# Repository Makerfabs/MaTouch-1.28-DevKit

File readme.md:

# MaTouch 1.28” ToolSets

```c++
/*
Version:		V1.0
Author:			Vincent
Create Date:	2024/9/26
Note:

*/
```

# Makerfabs

[Makerfabs home page](https://www.makerfabs.com/)

[Makerfabs Wiki](https://wiki.makerfabs.com/)

# MaTouch 1.28" DevKit

## Intruduce

MaTouch 1.28” ToolSets are series of ESP32-based products mainly consist of MaTouch 1.28” controller and kinds of functional expansion such as Dimmer/ Relay Controller/ Motor Driver, etc. It’s designed as tools to control/drive these actuators directly while also keep open hardware/software, which make it possible for users’ remaking and integration to other field projects.

[Wiki](https://wiki.makerfabs.com/Matouch%201.28%20DevKit.html)

## Part list

[Matouch 1.28" ToolSet_RGB LED Matrix](https://www.makerfabs.com/matouch-1-28-toolset-rgb-led-matrix.html)

[Matouch 1.28" ToolSet_LED Strip Controller](https://www.makerfabs.com/matouch-1-28-toolset-led-strip-controller.html)

[Matouch 1.28" ToolSet_Stepper Controller with TMC2209](https://www.makerfabs.com/matouch-1-28-toolset-stepper-controller-with-tmc2209.html)

[Matouch 1.28" ToolSet_Timer Switch Relay](https://www.makerfabs.com/matouch-1-28-toolset-timer-switch-relay.html)

[Matouch 1.28" ToolSet_DC Controller with H-Bridge](https://www.makerfabs.com/matouch-1-28-toolset-dc-controller-with-h-bridge.html)

[Matouch 1.28" ToolSet_AC Dimmer](https://www.makerfabs.com/matouch-1-28-toolset-ac-dimmer.html)

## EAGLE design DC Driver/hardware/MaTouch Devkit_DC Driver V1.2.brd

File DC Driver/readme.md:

# MaTouch1.28" Devkit DC Driver

```c++
/*
Library version:
Arduino IDE 2.3.4
esp32 V3.1.1
GFX Library for Arduino v1.5.3
lvgl v8.3.11
Adafruit INA219 v1.2.3
Adafruit BusIO v1.16.2

Tools:
USB CDC On Boot: Enabled
Flash size: 16MB(128Mb)
Partition Schrme: 16M Flash(3MB APP/9.9MB FATFS)
PSRAM: OPI PSRAM
*/
```
## Introduce

1.[How to use?](https://wiki.makerfabs.com/Matouch%201.28%20DevKit.html#26-dc-dimmer)

2.[How to upload code?](https://wiki.makerfabs.com/Matouch%201.28%20DevKit.html#36-dc-dimmer)

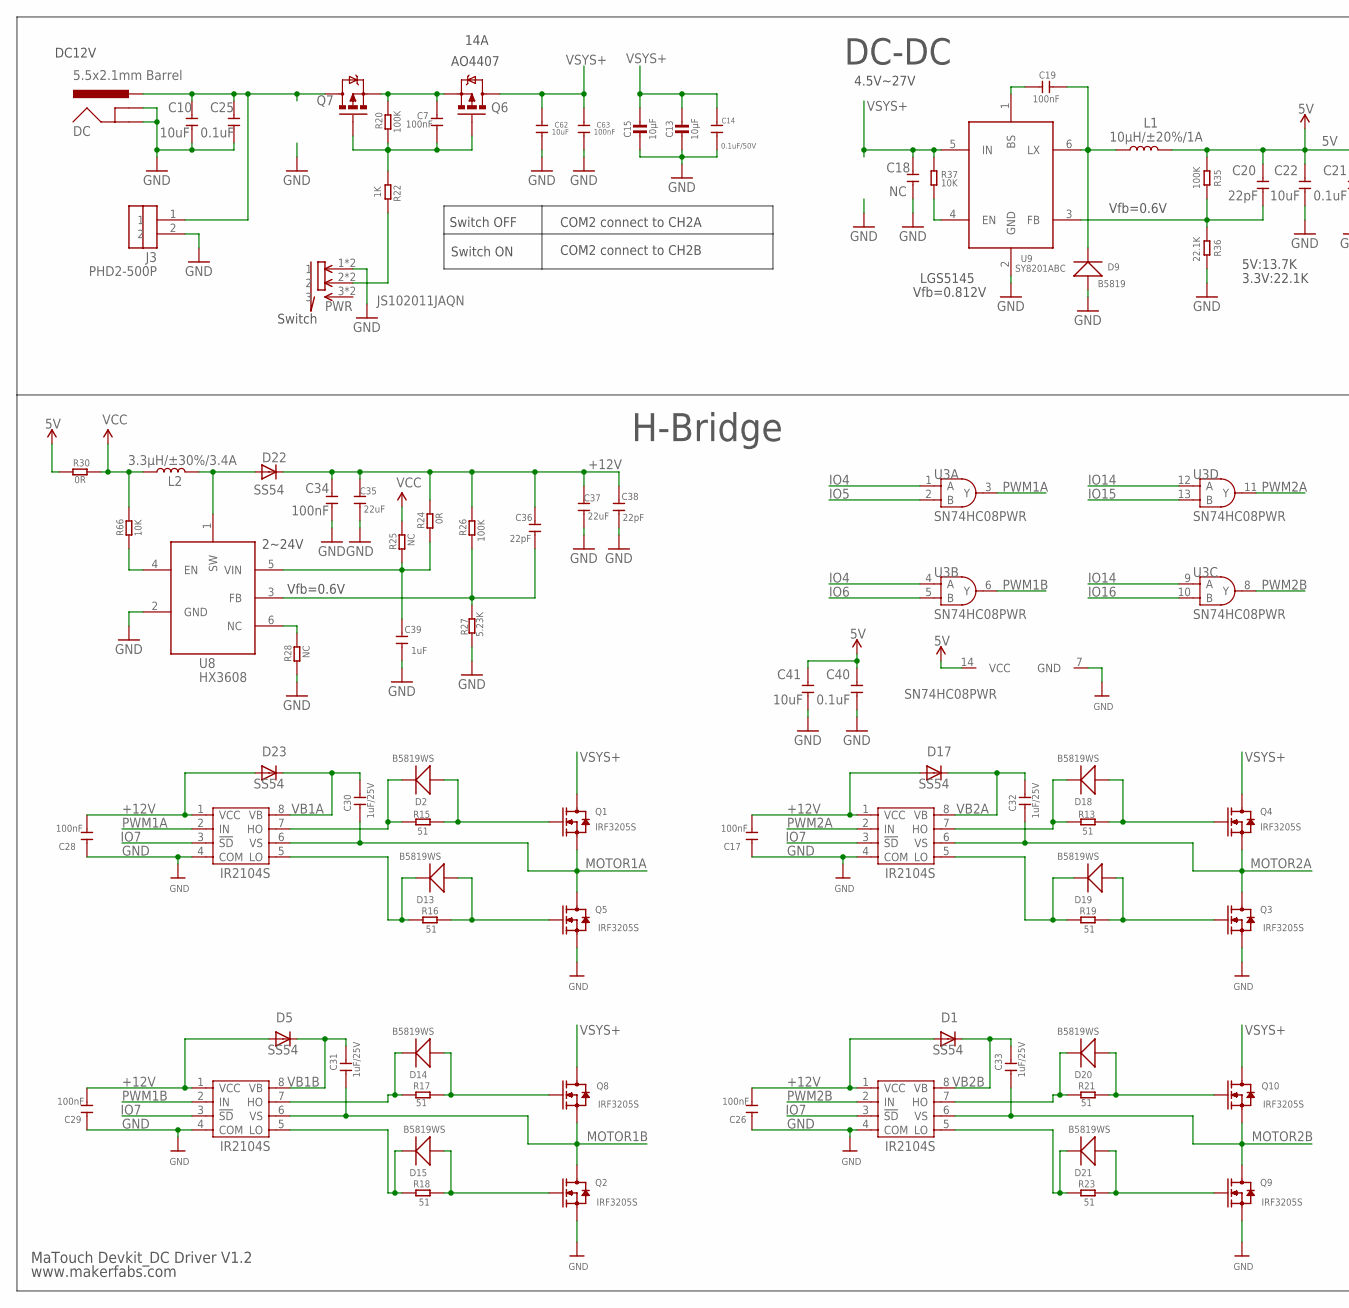
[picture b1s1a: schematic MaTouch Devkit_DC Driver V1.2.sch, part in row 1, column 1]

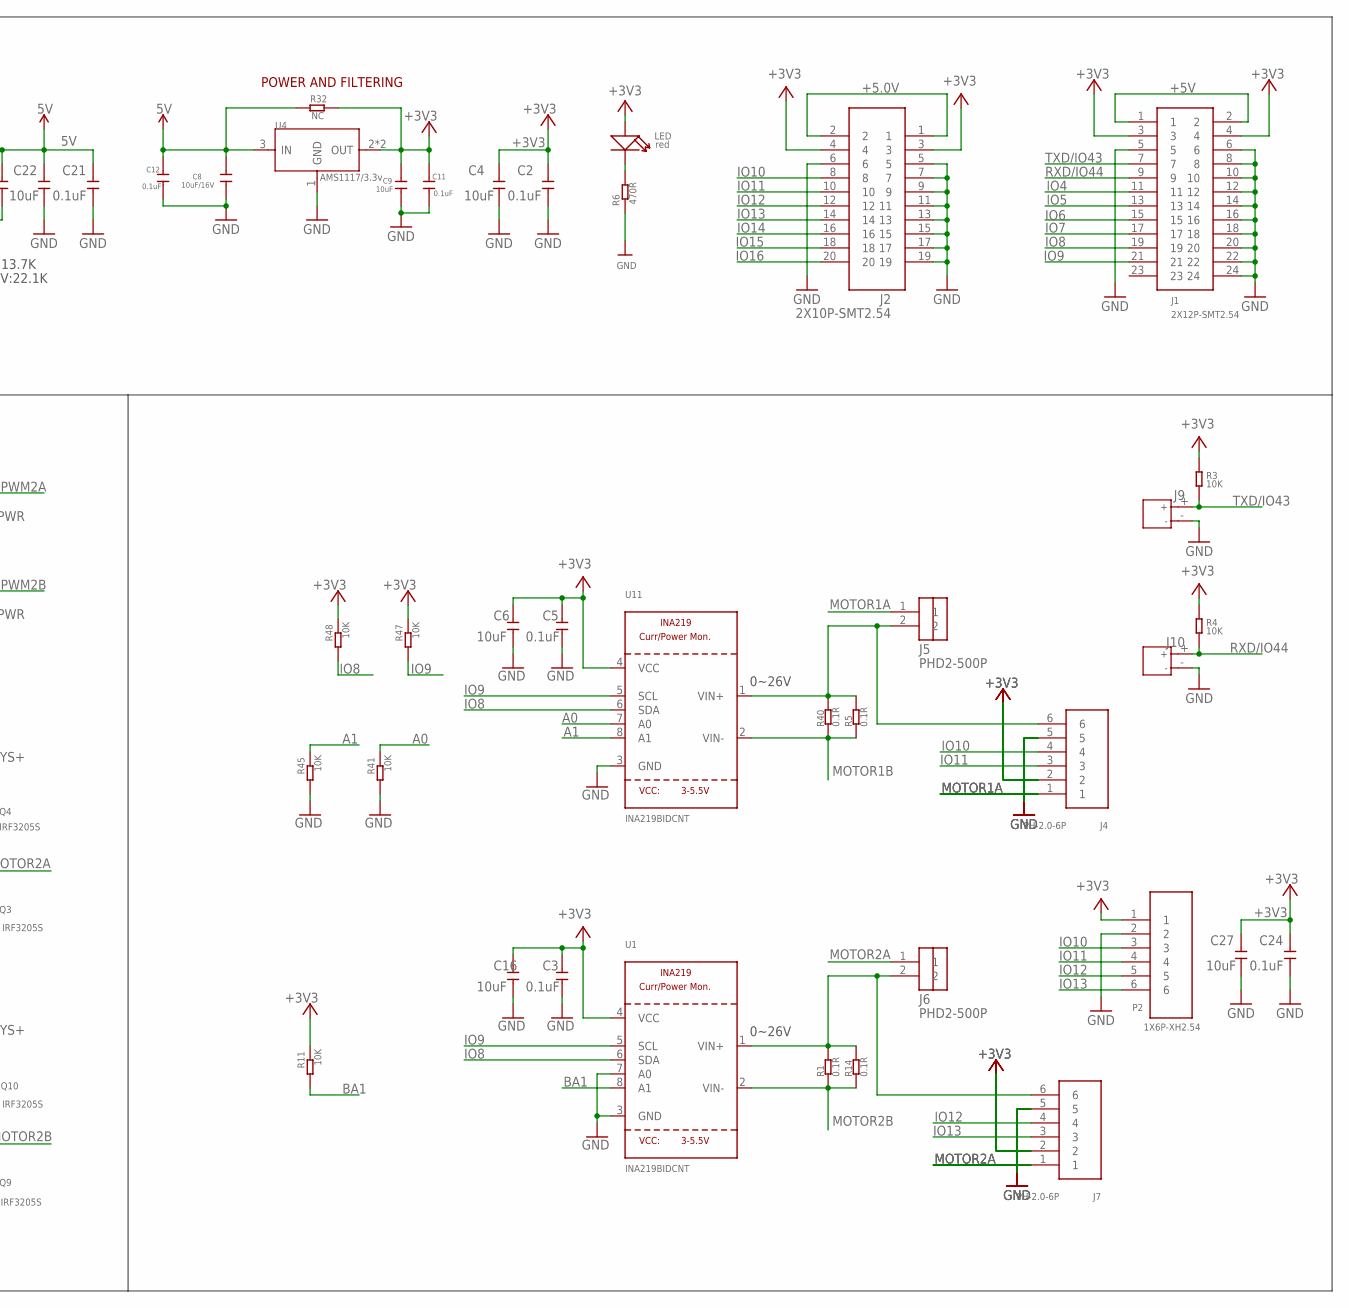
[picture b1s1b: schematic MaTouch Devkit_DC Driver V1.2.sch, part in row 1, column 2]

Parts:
C2, C3, C5, C11, C12, C21, C24, C25, C40: 0.1uF; 0603
C4, C6, C9, C10, C16, C22, C27, C41, C62: 10uF; 0603
C7, C17, C19, C26, C28, C29, C34, C63: 100nF; 0603
C8: 10uF/16V; 0603
C13, C15: 10µF; 0805-NO
C14: 0.1uF/50V; 0603
C18: NC; 0603
C20, C36, C38: 22pF; 0603
C30, C31, C32, C33: 1uF/25V; 0805
C35, C37: 22uF; DISCRETE_C0805
C39: 1uF; 0603
D1, D5, D17, D22, D23: SS54; DO-214AC
D2, D13, D14, D15, D18, D19, D20, D21: B5819WS; SOD323
D9: B5819; SOD123
DC: 5.5x2.1mm Barrel; POWER_JACK_SMD
J1: 2X12P-SMT2.54
J2: 2X10P-SMT2.54
J3, J5, J6: PHD2-500P; OPL_EAGLE_LIBRARY_2P-5.0
J4, J7: PH-2.0-6P
J9, J10: JACK-JST-2P-PW'2.54/90D'; JST-2P-2.54-90D
L1: 10µH/±20%/1A; SRN6045
L2: 3.3µH/±30%/3.4A; CR54
LED: red; DISCRETE_LED-0603
P2: 1X6P-XH2.54; 1*6P-XH2.54
PWR: JS102011JAQN; SMD-6-2.5MM
Q1, Q2, Q3, Q4, Q5, Q8, Q9, Q10: IRF3205S; TO263AB
Q6, Q7: MOSFET-PCHANNELFDS6675; SO08
R1, R5, R14, R40: 0.1R; DISCRETE_R2512
R3, R4, R11, R37, R41, R45, R47, R48, R66: 10K; R0603
R6: 470R; R0603
R13, R15, R16, R17, R18, R19, R21, R23: 51; R0805
R20, R26, R35: 100K; R0603
R22: 1K; R0603
R24, R30: 0R; R0603
R25, R28, R32: NC; R0603
R27: 5.23K; R0603
R36: 22.1K; R0603
U1, U11: INA219BIDCNT; SOT23-8
U2, U5, U6, U7: IR2104S; SOIC-8
U3: SN74HC08PWR; TSSOP14
U4: AMS1117/3.3v; SOT89
U8: HX3608; SOT-23-6
U9: SY8201ABC; SOT-23-6

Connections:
5V: C8.1, C12.2, C20.2, C21.2, C22.2, C40.2, C41.2, L1.2, R30.1, R32.1, R35.1, U3.14 (VCC), U4.3 (IN)
+3V3: C2.2, C3.2, C4.2, C5.2, C6.2, C9.1, C11.2, C16.2, C24.2, C27.2, J1.3, J1.4, J2.3, J2.4, J4.2, J7.2, LED.+, P2.1, R3.1, R4.1, R11.2, R32.2, R47.2, R48.2, U1.4 (VCC), U4.2 (OUT), U4.4 (OUT), U11.4 (VCC)
+5.0V: J2.1, J2.2
+5V: J1.1, J1.2
+12V: C17.2, C26.2, C28.2, C29.2, C34.2, C35.2, C36.2, C37.2, C38.2, D1.A, D5.A, D17.A, D22.C, D23.A, R24.2, R26.2, U2.1 (VCC), U5.1 (VCC), U6.1 (VCC), U7.1 (VCC)
A0: R41.2, U11.7 (A0)
A1: R45.2, U11.8 (A1)
BA1: R11.1, U1.8 (A1)
ENABLE: R66.1, U8.4 (EN)
GND: C2.1, C3.1, C4.1, C5.1, C6.1, C8.2, C9.2, C10.1, C11.1, C12.1, C13.2, C14.2, C15.2, C16.1, C17.1, C18.1, C21.1, C22.1, C24.1, C25.1, C26.1, C27.1, C28.1, C29.1, C34.1, C35.1, C37.1, C38.1, C39.1, C40.1, C41.1, C62.1, C63.1, D9.+, DC.GND (GNDBREAK), DC.P$4 (GND), J1.5, J1.6, J1.8, J1.10, J1.12, J1.14, J1.16, J1.18, J1.20, J1.22, J1.24, J2.5, J2.6, J2.7, J2.9, J2.11, J2.13, J2.15, J2.17, J2.19, J3.2, J4.5, J7.5, J9.-, J10.-, P2.2, PWR.1, PWR.1@1 (1), Q2.3 (S), Q3.3 (S), Q5.3 (S), Q9.3 (S), R6.1, R27.1, R28.1, R36.2, R41.1, R45.1, U1.3 (GND), U1.7 (A0), U2.4 (COM), U3.7 (GND), U4.1 (GND), U5.4 (COM), U6.4 (COM), U7.4 (COM), U8.2 (GND), U9.2 (GND), U11.3 (GND)
IO4: J1.11, U3.1 (A), U3.4 (A)
IO5: J1.13, U3.2 (B)
IO6: J1.15, U3.5 (B)
IO7: J1.17, U2.3 (!SD), U5.3 (!SD), U6.3 (!SD), U7.3 (!SD)
IO8: J1.19, R48.1, U1.6 (SDA), U11.6 (SDA)
IO9: J1.21, R47.1, U1.5 (SCL), U11.5 (SCL)
IO10: J2.8, J4.4, P2.3
IO11: J2.10, J4.3, P2.4
IO12: J2.12, J7.4, P2.5
IO13: J2.14, J7.3, P2.6
IO14: J2.16, U3.9 (A), U3.12 (A)
IO15: J2.18, U3.13 (B)
IO16: J2.20, U3.10 (B)
MOTOR1A: C30.1, J4.1, J5.1, Q1.3 (S), Q5.2 (D), U6.6 (VS)
MOTOR1B: C31.1, Q2.2 (D), Q8.3 (S), R5.1, R40.1, U7.6 (VS), U11.2 (VIN-)
MOTOR2A: C32.1, J6.1, J7.1, Q3.2 (D), Q4.3 (S), U2.6 (VS)
MOTOR2B: C33.1, Q9.2 (D), Q10.3 (S), R1.1, R14.1, U1.2 (VIN-), U5.6 (VS)
unnamed: D18.-, R13.1, U2.7 (HO)
unnamed: D19.-, R19.1, U2.5 (LO)
unnamed: J6.2, J7.6, R1.2, R14.2, U1.1 (VIN+)
unnamed: D18.+, Q4.1 (G), R13.2
unnamed: LED.-, R6.2
unnamed: J4.6, J5.2, R5.2, R40.2, U11.1 (VIN+)
unnamed: C7.1, Q6.4 (G), Q7.4 (G), R20.2, R22.2
unnamed: PWR.2, PWR.2@1 (2), R22.1
unnamed: C10.2, C25.2, DC.VIN0 (PWR), J3.1, Q7.5 (D), Q7.6 (D), Q7.7 (D), Q7.8 (D)
unnamed: D19.+, Q3.1 (G), R19.2
unnamed: D20.-, R21.1, U5.7 (HO)
unnamed: D2.-, R15.1, U6.7 (HO)
unnamed: D13.-, R16.1, U6.5 (LO)
unnamed: D2.+, Q1.1 (G), R15.2
unnamed: D13.+, Q5.1 (G), R16.2
unnamed: D14.-, R17.1, U7.7 (HO)
unnamed: D15.-, R18.1, U7.5 (LO)
unnamed: D14.+, Q8.1 (G), R17.2
unnamed: D15.+, Q2.1 (G), R18.2
unnamed: D21.-, R23.1, U5.5 (LO)
unnamed: D20.+, Q10.1 (G), R21.2
unnamed: D21.+, Q9.1 (G), R23.2
unnamed: D22.A, L2.P$2 (2), U8.1 (SW)
unnamed: C39.2, R24.1, R25.1, U8.5 (VIN)
unnamed: C36.1, R26.1, R27.2, U8.3 (FB)
unnamed: R28.2, U8.6 (NC)
unnamed: C19.2, D9.-, L1.1, U9.6 (LX)
unnamed: C19.1, U9.1 (BS)
unnamed: C20.1, R35.2, R36.1, U9.3 (FB)
unnamed: R37.2, U9.4 (EN)
unnamed: C7.2, Q6.1 (S), Q6.2 (S), Q6.3 (S), Q7.1 (S), Q7.2 (S), Q7.3 (S), R20.1
PWM1A: U3.3 (Y), U6.2 (IN)
PWM1B: U3.6 (Y), U7.2 (IN)
PWM2A: U2.2 (IN), U3.11 (Y)
PWM2B: U3.8 (Y), U5.2 (IN)
RXD/IO44: J1.9, J10.+, R4.2
TXD/IO43: J1.7, J9.+, R3.2
VB1A: C30.2, D23.C, U6.8 (VB)
VB1B: C31.2, D5.C, U7.8 (VB)
VB2A: C32.2, D17.C, U2.8 (VB)
VB2B: C33.2, D1.C, U5.8 (VB)
VCC: L2.P$1 (1), R25.2, R30.2, R66.2
VSYS+: C13.1, C14.1, C15.1, C18.2, C62.2, C63.2, Q1.2 (D), Q4.2 (D), Q6.5 (D), Q6.6 (D), Q6.7 (D), Q6.8 (D), Q8.2 (D), Q10.2 (D), R37.1, U9.5 (IN)

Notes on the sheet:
MaTouch Devkit_DC Driver V1.2
www.makerfabs.com
DC-DC
Switch OFF
Switch ON
COM2 connect to CH2A
COM2 connect to CH2B
Vfb=0.6V
4.5V~27V
DC12V
AO4407
14A
POWER AND FILTERING
H-Bridge
0~26V
LGS5145
2~24V
Switch
5V:13.7K
3.3V:22.1K
Vfb=0.812V

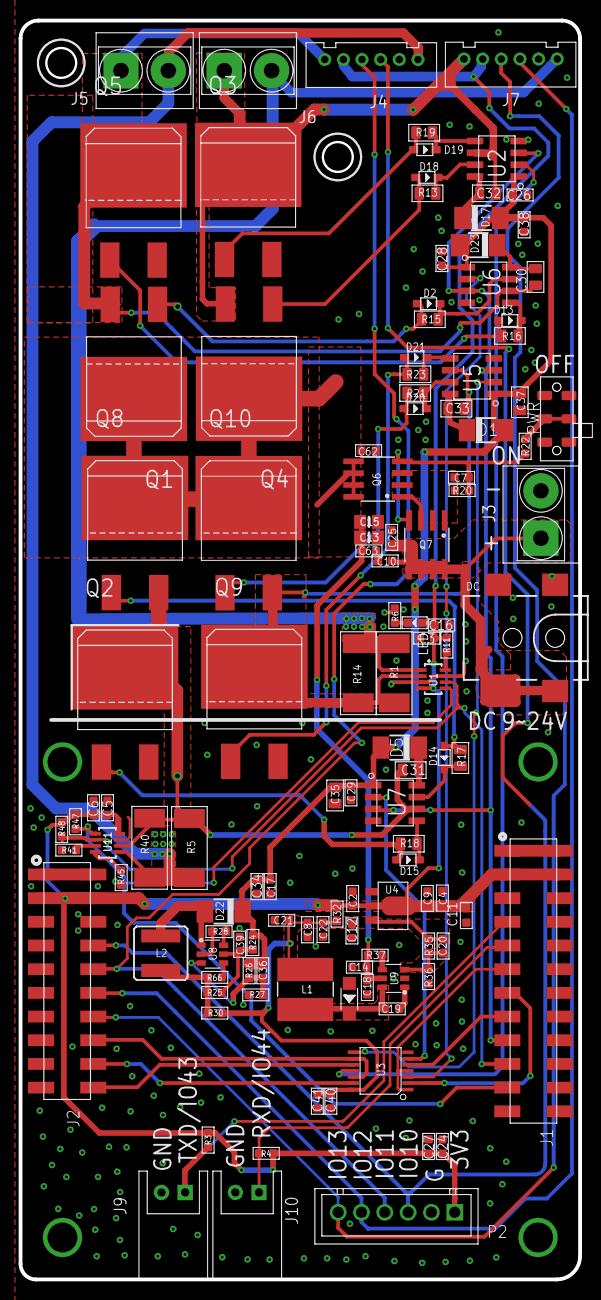
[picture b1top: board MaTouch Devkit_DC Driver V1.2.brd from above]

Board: 2 copper layers, 60.0 x 135.0 mm, 124 parts (1 on the bottom side), 70 nets.

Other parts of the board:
U$2: MAKERFABS_0.3

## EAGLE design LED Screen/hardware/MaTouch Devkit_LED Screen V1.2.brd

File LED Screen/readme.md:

# MaTouch1.28" Devkit LED Screen

```c++
/*
Library version:
Arduino IDE 2.3.4
esp32 V3.1.1
GFX Library for Arduino v1.5.3
lvgl v8.3.11
ESP32 HUB75 LED MATRIX PANEL DMA Display v3.0.11
Adafruit GFX Library v1.11.11
Adafruit BusIO v1.16.2
AnimatedGIF v2.1.1

Tools:
USB CDC On Boot: Enabled
Flash size: 16MB(128Mb)
Partition Schrme: 16M Flash(3MB APP/9.9MB FATFS)
PSRAM: OPI PSRAM
*/
```
## Introduce

1.[How to use?](https://wiki.makerfabs.com/Matouch%201.28%20DevKit.html#22-rgb-matrix-panel-driver)

2.[How to upload code?](https://wiki.makerfabs.com/Matouch%201.28%20DevKit.html#32-rgb-matrix-panel-driver)

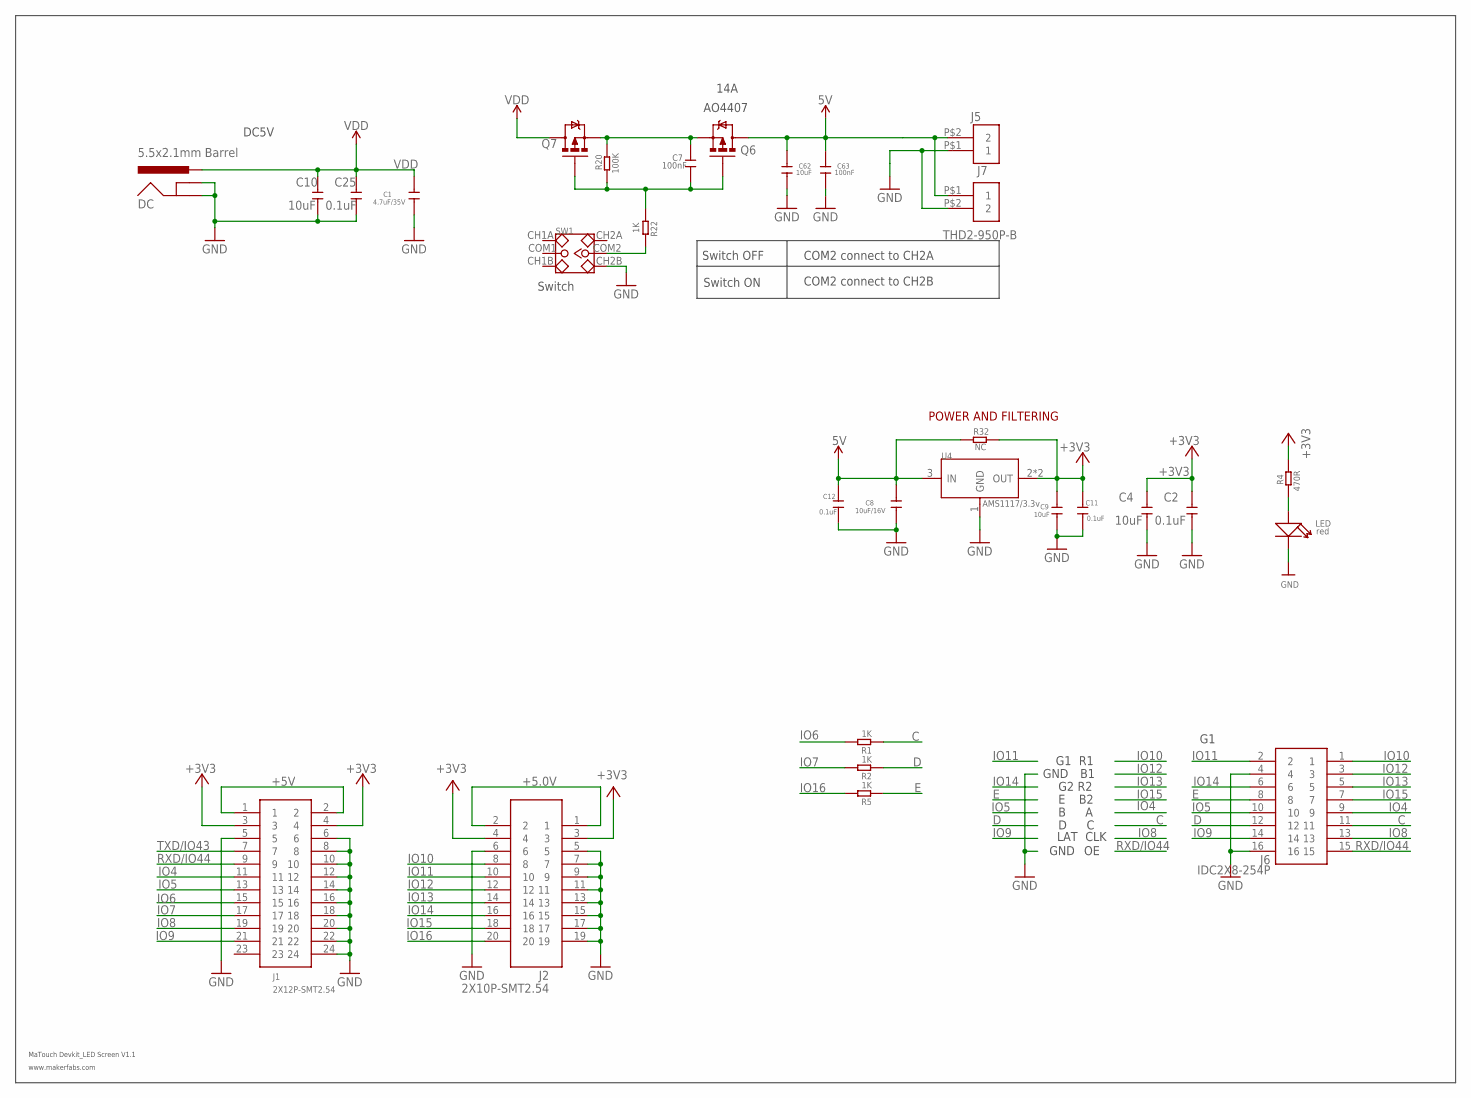
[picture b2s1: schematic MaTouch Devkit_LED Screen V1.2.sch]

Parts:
C1: 4.7uF/35V; 0603
C2, C11, C12, C25: 0.1uF; 0603
C4, C9, C10, C62: 10uF; 0603
C7, C63: 100nF; 0603
C8: 10uF/16V; 0603
DC: 5.5x2.1mm Barrel; POWER_JACK_SMD
J1: 2X12P-SMT2.54
J2: 2X10P-SMT2.54
J5: THD2-950P-2050L1620W1670H
J6: IDC2X8-254P; IDC2X8-254P-2792L1330W890H
J7: THD2-950P-B; THD2-950P-2100L1580W1780H
LED: red; DISCRETE_LED-0603
Q6, Q7: MOSFET-PCHANNELFDS6675; SO08
R1, R2, R5, R22: 1K; R0603
R4: 470R; R0603
R20: 100K; R0603
R32: NC; R0603
SW1: SWITCH-2CH-6P'90D'; 6P-2CH-2.54-9.0X3.6-90D
U4: AMS1117/3.3v; SOT89

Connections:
5V: C8.1, C12.2, C62.2, C63.2, J5.P$2 (2), J7.P$1 (1), Q6.5 (D), Q6.6 (D), Q6.7 (D), Q6.8 (D), R32.1, U4.3 (IN)
+3V3: C2.2, C4.2, C9.1, C11.2, J1.3, J1.4, J2.3, J2.4, R4.2, R32.2, U4.2 (OUT), U4.4 (OUT)
+5.0V: J2.1, J2.2
+5V: J1.1, J1.2
C: J6.11, R1.1
D: J6.12, R2.1
E: J6.8, R5.1
GND: C1.2, C2.1, C4.1, C8.2, C9.2, C10.1, C11.1, C12.1, C25.1, C62.1, C63.1, DC.GND (GNDBREAK), DC.P$4 (GND), J1.5, J1.6, J1.8, J1.10, J1.12, J1.14, J1.16, J1.18, J1.20, J1.22, J1.24, J2.5, J2.6, J2.7, J2.9, J2.11, J2.13, J2.15, J2.17, J2.19, J5.P$1 (1), J6.4, J6.16, J7.P$2 (2), LED.-, SW1.CH2B, U4.1 (GND)
IO4: J1.11, J6.9
IO5: J1.13, J6.10
IO6: J1.15, R1.2
IO7: J1.17, R2.2
IO8: J1.19, J6.13
IO9: J1.21, J6.14
IO10: J2.8, J6.1
IO11: J2.10, J6.2
IO12: J2.12, J6.3
IO13: J2.14, J6.5
IO14: J2.16, J6.6
IO15: J2.18, J6.7
IO16: J2.20, R5.2
unnamed: LED.+, R4.1
unnamed: C7.1, Q6.4 (G), Q7.4 (G), R20.2, R22.2
unnamed: R22.1, SW1.COM2
unnamed: C7.2, Q6.1 (S), Q6.2 (S), Q6.3 (S), Q7.1 (S), Q7.2 (S), Q7.3 (S), R20.1
RXD/IO44: J1.9, J6.15
TXD/IO43: J1.7
VDD: C1.1, C10.2, C25.2, DC.VIN0 (PWR), Q7.5 (D), Q7.6 (D), Q7.7 (D), Q7.8 (D)

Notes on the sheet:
MaTouch Devkit_LED Screen V1.1
www.makerfabs.com
Switch OFF
Switch ON
COM2 connect to CH2A
COM2 connect to CH2B
DC5V
AO4407
14A
Switch
POWER AND FILTERING
LAT
CLK
GND

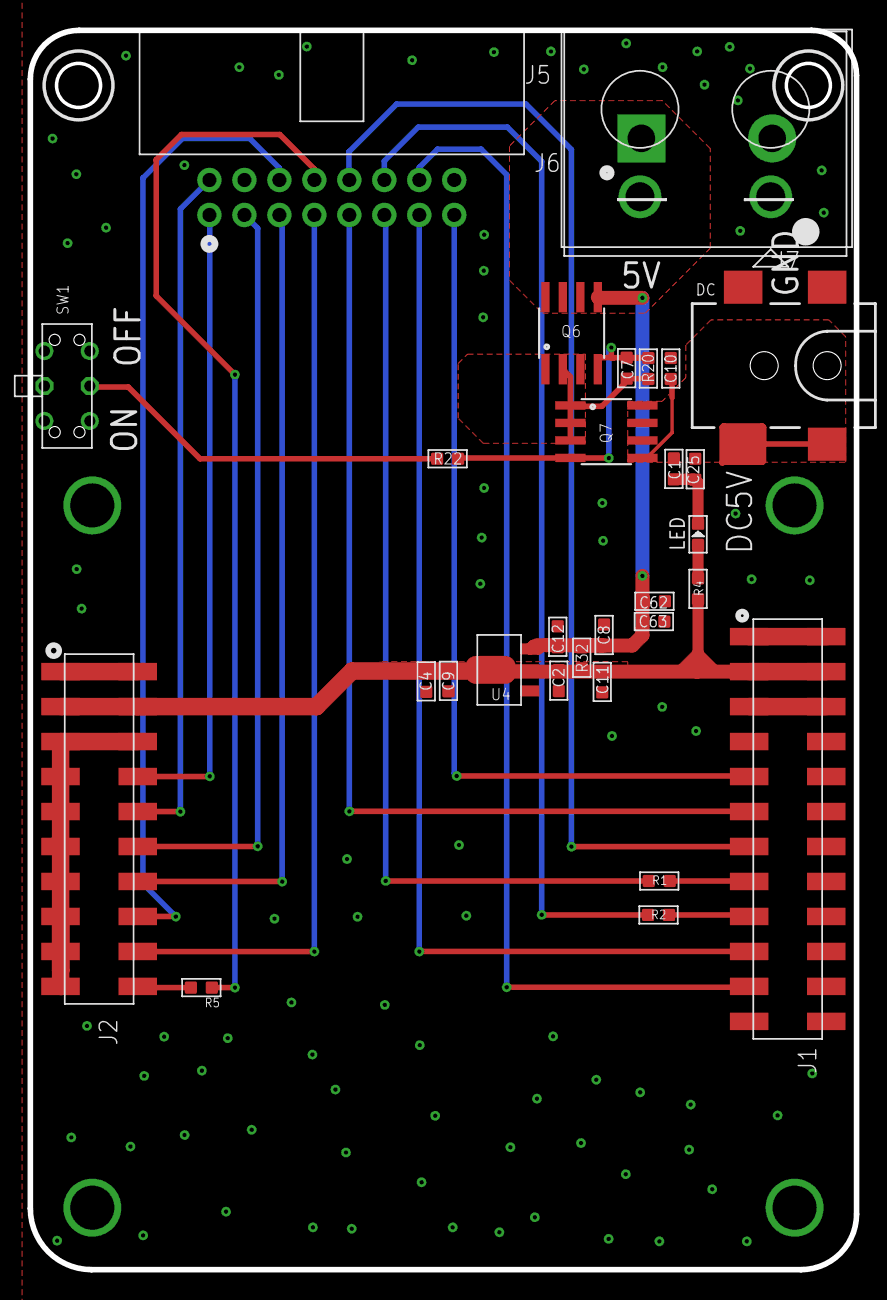
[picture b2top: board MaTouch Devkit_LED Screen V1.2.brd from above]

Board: 2 copper layers, 60.0 x 90.0 mm, 31 parts (1 on the bottom side), 27 nets.

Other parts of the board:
U$2: MAKERFABS_0.3

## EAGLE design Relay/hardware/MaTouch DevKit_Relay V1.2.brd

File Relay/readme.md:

# MaTouch1.28" DevKit Relay

```c++
/*
Library version:
Arduino IDE 2.3.4
esp32 V3.1.1
GFX Library for Arduino v1.5.3
lvgl v8.3.11
RTClib v2.1.4
Adafruit BusIO v1.16.2
ESP32Time v2.0.6

Tools:
USB CDC On Boot: Enabled
Flash size: 16MB(128Mb)
Partition Schrme: 16M Flash(3MB APP/9.9MB FATFS)
PSRAM: OPI PSRAM
*/
```
## Introduce

1.[How to use?](https://wiki.makerfabs.com/Matouch%201.28%20DevKit.html#24-relay-with-8-channels)

2.[How to upload code?](https://wiki.makerfabs.com/Matouch%201.28%20DevKit.html#34-relay-with-8-channels)

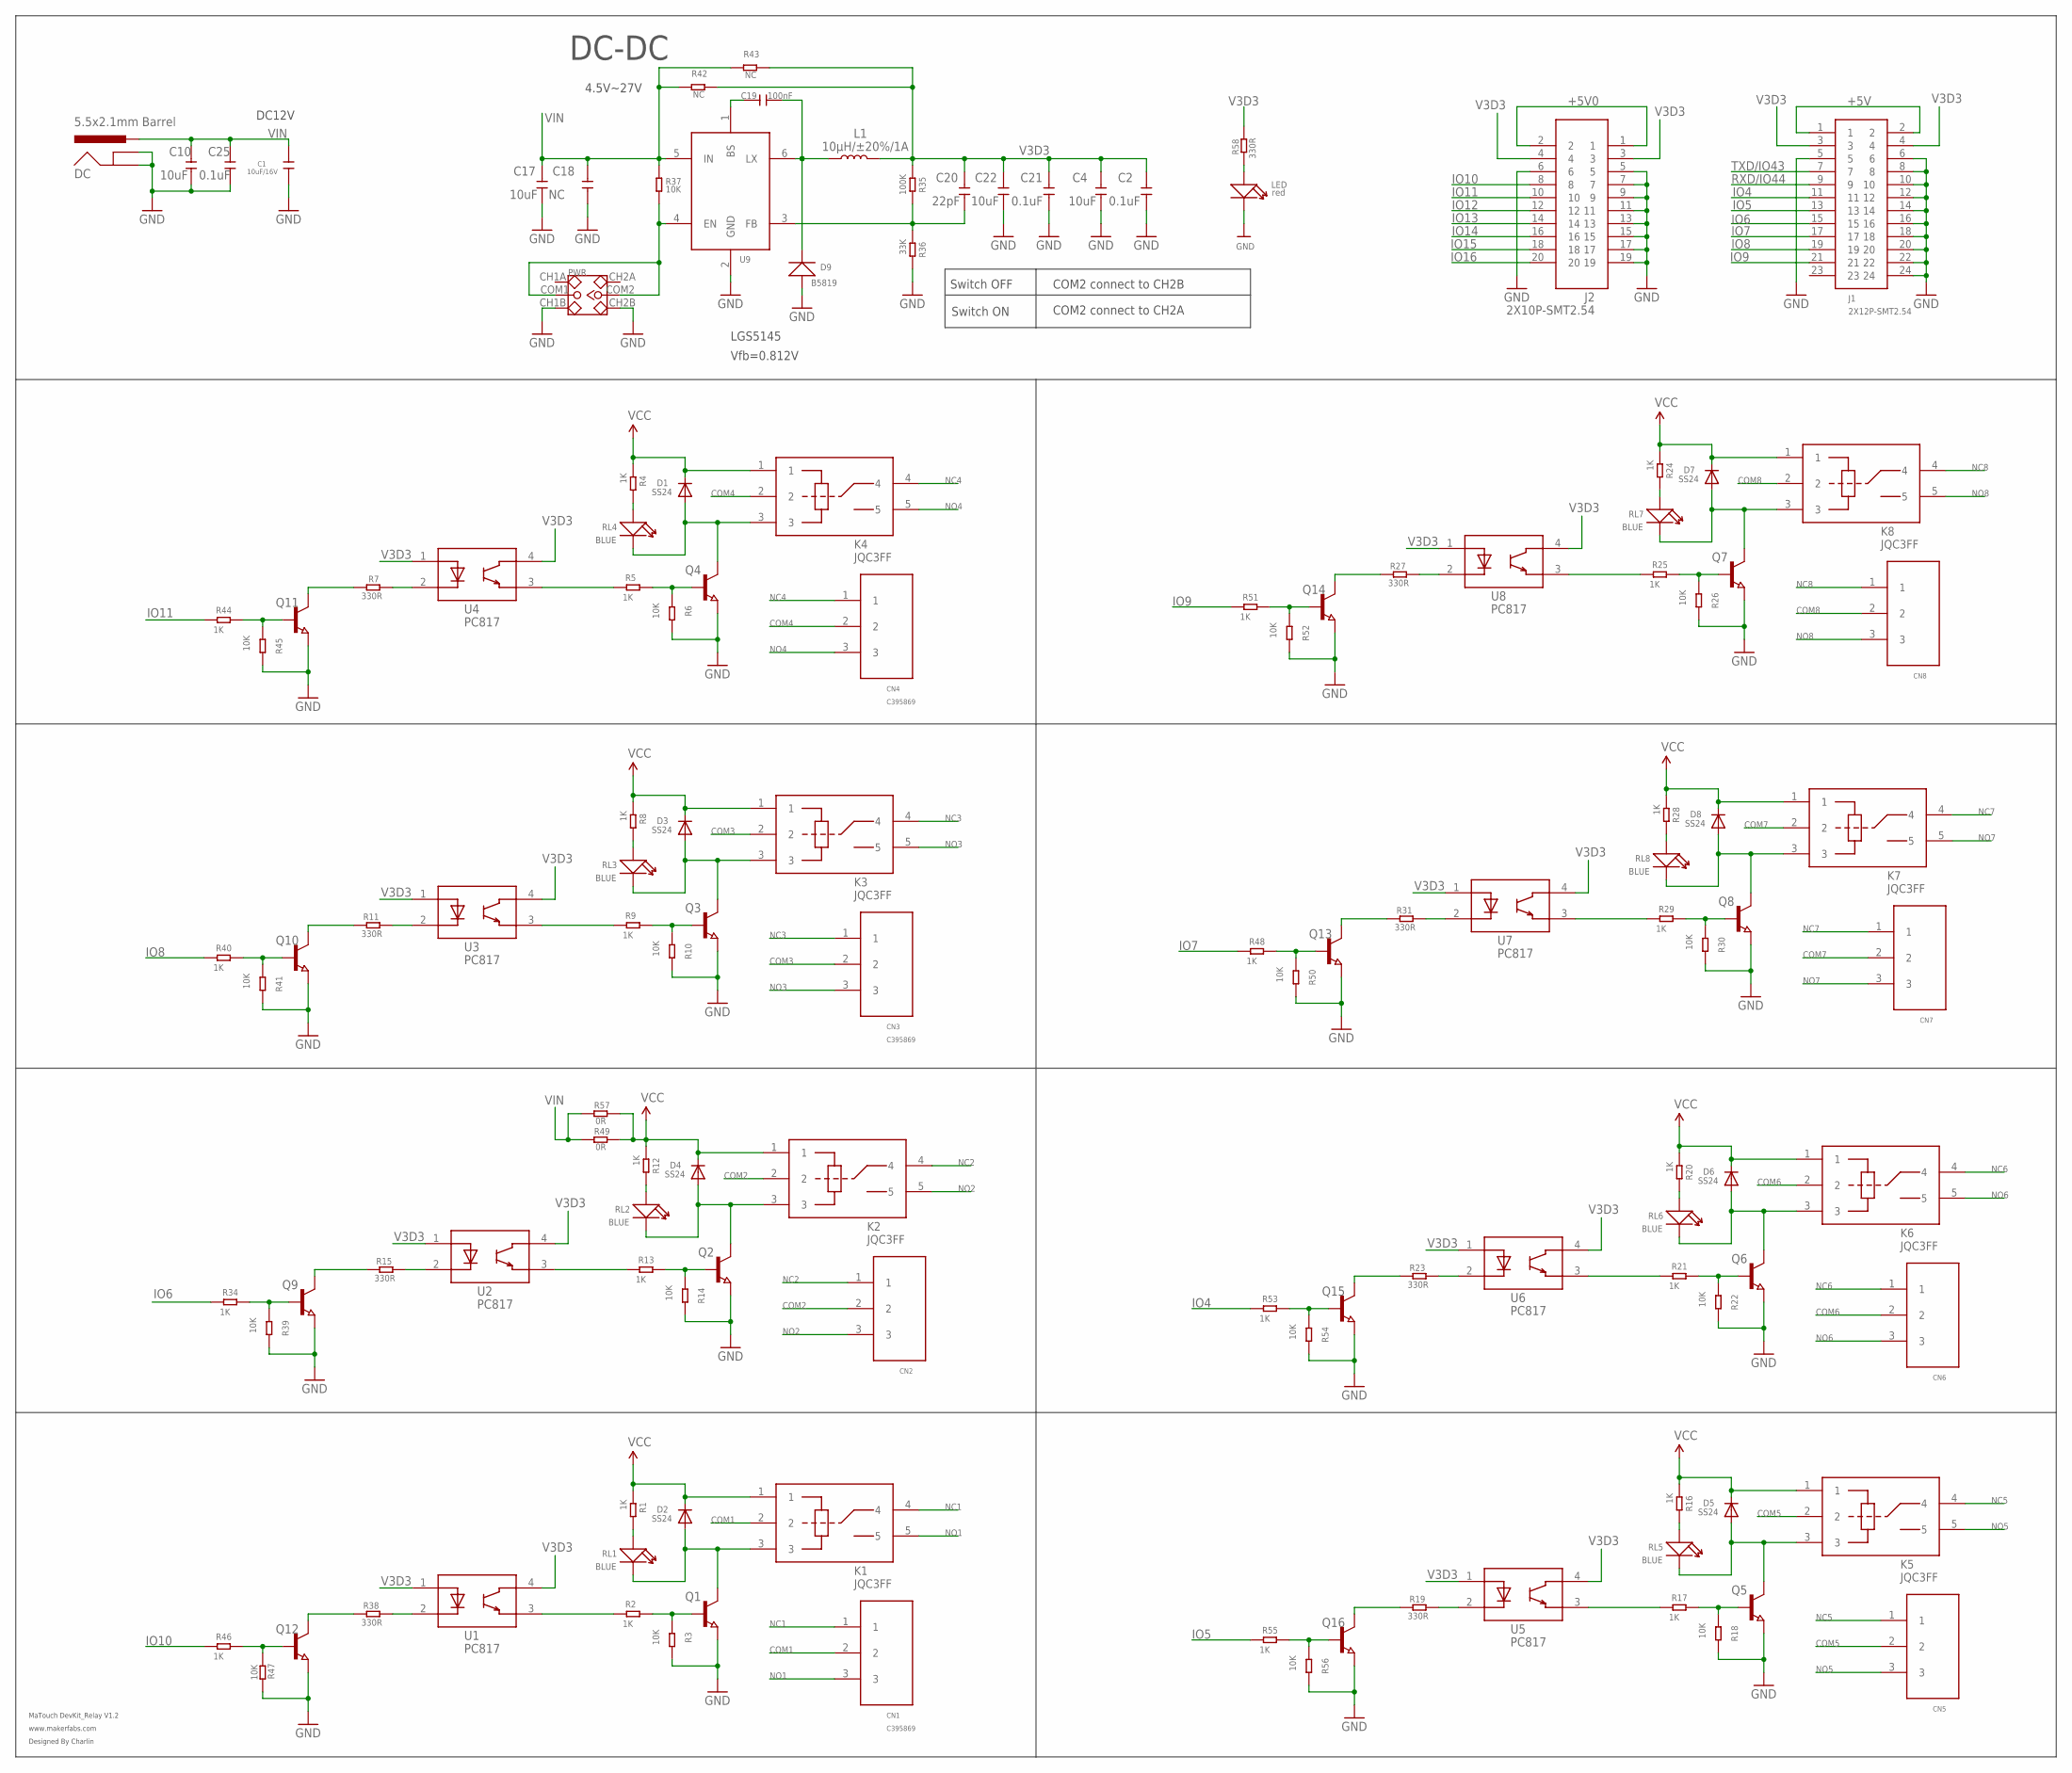
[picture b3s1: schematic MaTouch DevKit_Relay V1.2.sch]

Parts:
C1: 10uF/16V; 0603
C2, C21, C25: 0.1uF; 0603
C4, C10, C17, C22: 10uF; 0603
C18: NC; 0603
C19: 100nF; 0603
C20: 22pF; 0603
CN1, CN2, CN3, CN4, CN5, CN6, CN7, CN8: C395869; PIN_3P
D1, D2, D3, D4, D5, D6, D7, D8: SS24; SMADIODE
D9: B5819; SOD123
DC: 5.5x2.1mm Barrel; POWER_JACK_SMD
J1: 2X12P-SMT2.54
J2: 2X10P-SMT2.54
K1, K2, K3, K4, K5, K6, K7, K8: JQC3FF; DIP5_JQC3FF
L1: 10µH/±20%/1A; SRN6045
LED: red; DISCRETE_LED-0603
PWR: SWITCH-2CH-6P; 6P-2CH-2.54-7.6X3.0
Q1, Q2, Q3, Q4, Q5, Q6, Q7, Q8, Q9, Q10, Q11, Q12, Q13, Q14, Q15, Q16: NPN-TRANSISTOR_SOT23; SOT23
R1, R2, R4, R5, R8, R9, R12, R13, R16, R17, R20, R21, R24, R25, R28, R29, R34, R40, R44, R46, R48, R51, R53, R55: 1K; R0603
R3, R6, R10, R14, R18, R22, R26, R30, R37, R39, R41, R45, R47, R50, R52, R54, R56: 10K; R0603
R7, R11, R15, R19, R23, R27, R31, R38, R58: 330R; R0603
R35: 100K; R0603
R36: 33K; R0603
R42, R43: NC; R0603
R49, R57: 0R; R0603
RL1, RL2, RL3, RL4, RL5, RL6, RL7, RL8: BLUE; LED-0603
U1, U2, U3, U4, U5, U6, U7, U8: PC817; SMD4-254P-1016L460W
U9: SY8201ABC; SOT-23-6

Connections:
+5V: J1.1, J1.2
+5V0: J2.1, J2.2
COM1: CN1.2, K1.2
COM2: CN2.2, K2.2
COM3: CN3.2, K3.2
COM4: CN4.2, K4.2
COM5: CN5.2, K5.2
COM6: CN6.2, K6.2
COM7: CN7.2, K7.2
COM8: CN8.2, K8.2
GND: C1.2, C2.1, C4.1, C10.1, C17.1, C18.1, C21.1, C22.1, C25.1, D9.+, DC.GND (GNDBREAK), DC.P$4 (GND), J1.5, J1.6, J1.8, J1.10, J1.12, J1.14, J1.16, J1.18, J1.20, J1.22, J1.24, J2.5, J2.6, J2.7, J2.9, J2.11, J2.13, J2.15, J2.17, J2.19, LED.-, PWR.CH1B, PWR.CH2B, Q1.2 (E), Q2.2 (E), Q3.2 (E), Q4.2 (E), Q5.2 (E), Q6.2 (E), Q7.2 (E), Q8.2 (E), Q9.2 (E), Q10.2 (E), Q11.2 (E), Q12.2 (E), Q13.2 (E), Q14.2 (E), Q15.2 (E), Q16.2 (E), R3.2, R6.2, R10.2, R14.2, R18.2, R22.2, R26.2, R30.2, R36.2, R39.2, R41.2, R45.2, R47.2, R50.2, R52.2, R54.2, R56.2, U9.2 (GND)
IO4: J1.11, R53.1
IO5: J1.13, R55.1
IO6: J1.15, R34.1
IO7: J1.17, R48.1
IO8: J1.19, R40.1
IO9: J1.21, R51.1
IO10: J2.8, R46.1
IO11: J2.10, R44.1
IO12: J2.12
IO13: J2.14
IO14: J2.16
IO15: J2.18
IO16: J2.20
unnamed: R2.1, U1.3
unnamed: R4.2, RL4.+
unnamed: R1.2, RL1.+
unnamed: D1.A, K4.3, Q4.3 (C), RL4.-
unnamed: Q4.1 (B), R5.2, R6.1
unnamed: R7.2, U4.2
unnamed: R5.1, U4.3
unnamed: R8.2, RL3.+
unnamed: D2.A, K1.3, Q1.3 (C), RL1.-
unnamed: D3.A, K3.3, Q3.3 (C), RL3.-
unnamed: Q3.1 (B), R9.2, R10.1
unnamed: R11.2, U3.2
unnamed: R9.1, U3.3
unnamed: Q1.1 (B), R2.2, R3.1
unnamed: R12.2, RL2.+
unnamed: D4.A, K2.3, Q2.3 (C), RL2.-
unnamed: Q2.1 (B), R13.2, R14.1
unnamed: R15.2, U2.2
unnamed: R13.1, U2.3
unnamed: R16.2, RL5.+
unnamed: D5.A, K5.3, Q5.3 (C), RL5.-
unnamed: Q5.1 (B), R17.2, R18.1
unnamed: R19.2, U5.2
unnamed: R17.1, U5.3
unnamed: R20.2, RL6.+
unnamed: D6.A, K6.3, Q6.3 (C), RL6.-
unnamed: Q6.1 (B), R21.2, R22.1
unnamed: R23.2, U6.2
unnamed: R21.1, U6.3
unnamed: R24.2, RL7.+
unnamed: D7.A, K8.3, Q7.3 (C), RL7.-
unnamed: Q7.1 (B), R25.2, R26.1
unnamed: R38.2, U1.2
unnamed: R27.2, U8.2
unnamed: R25.1, U8.3
unnamed: R28.2, RL8.+
unnamed: D8.A, K7.3, Q8.3 (C), RL8.-
unnamed: Q8.1 (B), R29.2, R30.1
unnamed: R31.2, U7.2
unnamed: R29.1, U7.3
unnamed: C19.2, D9.-, L1.1, U9.6 (LX)
unnamed: C19.1, U9.1 (BS)
unnamed: C20.1, R35.2, R36.1, U9.3 (FB)
unnamed: PWR.COM1, PWR.COM2, R37.2, U9.4 (EN)
unnamed: LED.+, R58.1
unnamed: Q9.1 (B), R34.2, R39.1
unnamed: Q9.3 (C), R15.1
unnamed: Q10.1 (B), R40.2, R41.1
unnamed: Q10.3 (C), R11.1
unnamed: Q11.1 (B), R44.2, R45.1
unnamed: Q11.3 (C), R7.1
unnamed: Q12.1 (B), R46.2, R47.1
unnamed: Q12.3 (C), R38.1
unnamed: Q13.1 (B), R48.2, R50.1
unnamed: Q13.3 (C), R31.1
unnamed: Q14.1 (B), R51.2, R52.1
unnamed: Q14.3 (C), R27.1
unnamed: Q15.1 (B), R53.2, R54.1
unnamed: Q15.3 (C), R23.1
unnamed: Q16.1 (B), R55.2, R56.1
unnamed: Q16.3 (C), R19.1
NC1: CN1.1, K1.4
NC2: CN2.1, K2.4
NC3: CN3.1, K3.4
NC4: CN4.1, K4.4
NC5: CN5.1, K5.4
NC6: CN6.1, K6.4
NC7: CN7.1, K7.4
NC8: CN8.1, K8.4
NO1: CN1.3, K1.5
NO2: CN2.3, K2.5
NO3: CN3.3, K3.5
NO4: CN4.3, K4.5
NO5: CN5.3, K5.5
NO6: CN6.3, K6.5
NO7: CN7.3, K7.5
NO8: CN8.3, K8.5
RXD/IO44: J1.9
TXD/IO43: J1.7
V3D3: C2.2, C4.2, C20.2, C21.2, C22.2, J1.3, J1.4, J2.3, J2.4, L1.2, R35.1, R42.2, R43.2, R58.2, U1.1, U1.4, U2.1, U2.4, U3.1, U3.4, U4.1, U4.4, U5.1, U5.4, U6.1, U6.4, U7.1, U7.4, U8.1, U8.4
VCC: D1.C, D2.C, D3.C, D4.C, D5.C, D6.C, D7.C, D8.C, K1.1, K2.1, K3.1, K4.1, K5.1, K6.1, K7.1, K8.1, R1.1, R4.1, R8.1, R12.1, R16.1, R20.1, R24.1, R28.1, R49.2, R57.2
VIN: C1.1, C10.2, C17.2, C18.2, C25.2, DC.VIN0 (PWR), R37.1, R42.1, R43.1, R49.1, R57.1, U9.5 (IN)

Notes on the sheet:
MaTouch DevKit_Relay V1.2
www.makerfabs.com
DC-DC
Switch OFF
Switch ON
COM2 connect to CH2B
COM2 connect to CH2A
DC12V
Vfb=0.812V
4.5V~27V
LGS5145
Designed By Charlin

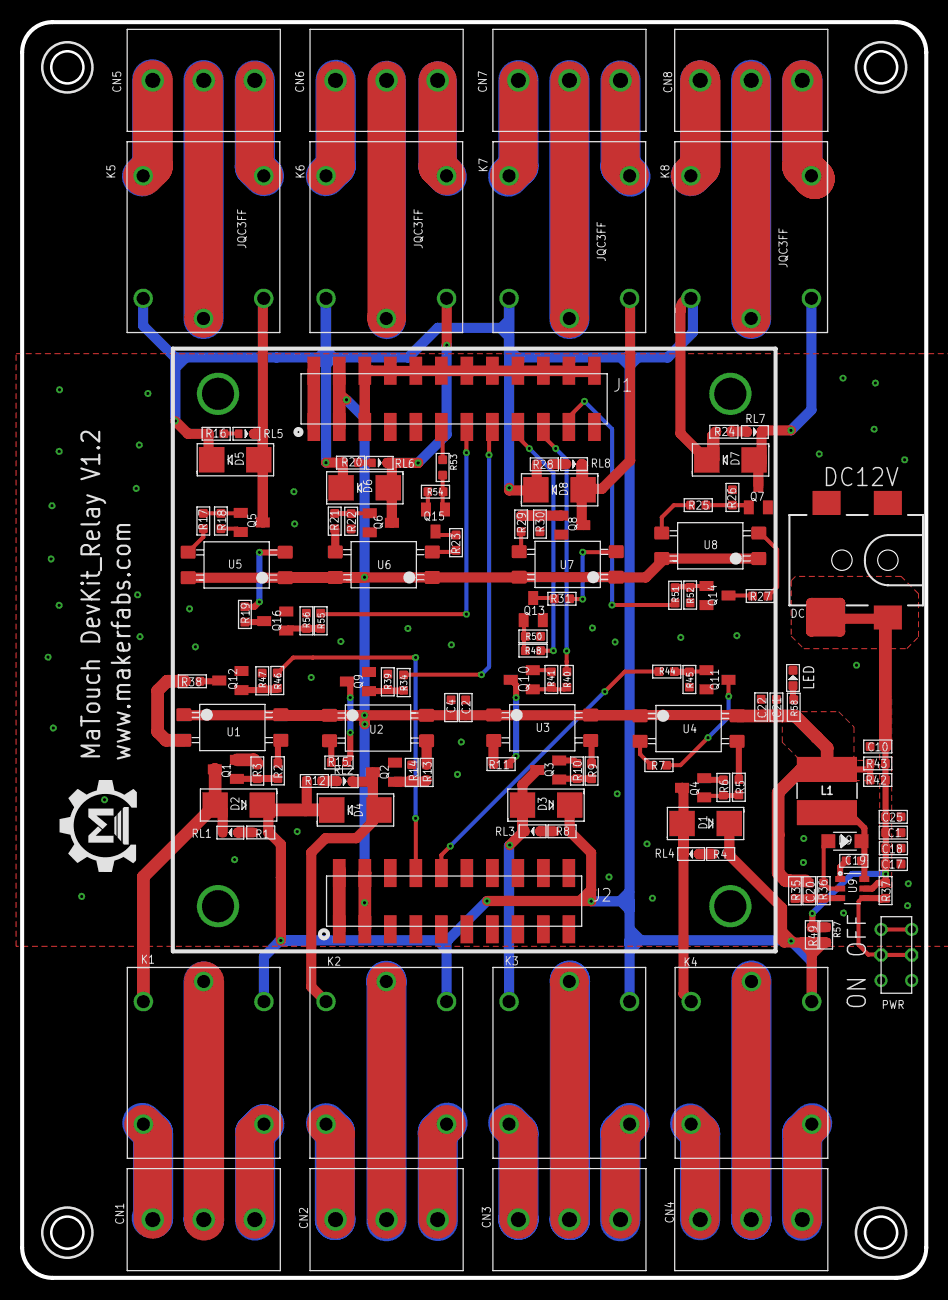
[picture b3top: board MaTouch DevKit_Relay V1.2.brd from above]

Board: 2 copper layers, 90.0 x 125.0 mm, 132 parts (0 on the bottom side), 99 nets.

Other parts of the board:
U$2: MAKERFABS_0.3

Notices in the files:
parts and their libraries:
SparkFun-Resistors: Licensing: Creative Commons ShareAlike 4.0 International - https://creativecommons.org/licenses/by-sa/4.0
microbuilder: This work is placed in the public domain, and may be freely used for commercial and non-commercial work with the following conditions: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
